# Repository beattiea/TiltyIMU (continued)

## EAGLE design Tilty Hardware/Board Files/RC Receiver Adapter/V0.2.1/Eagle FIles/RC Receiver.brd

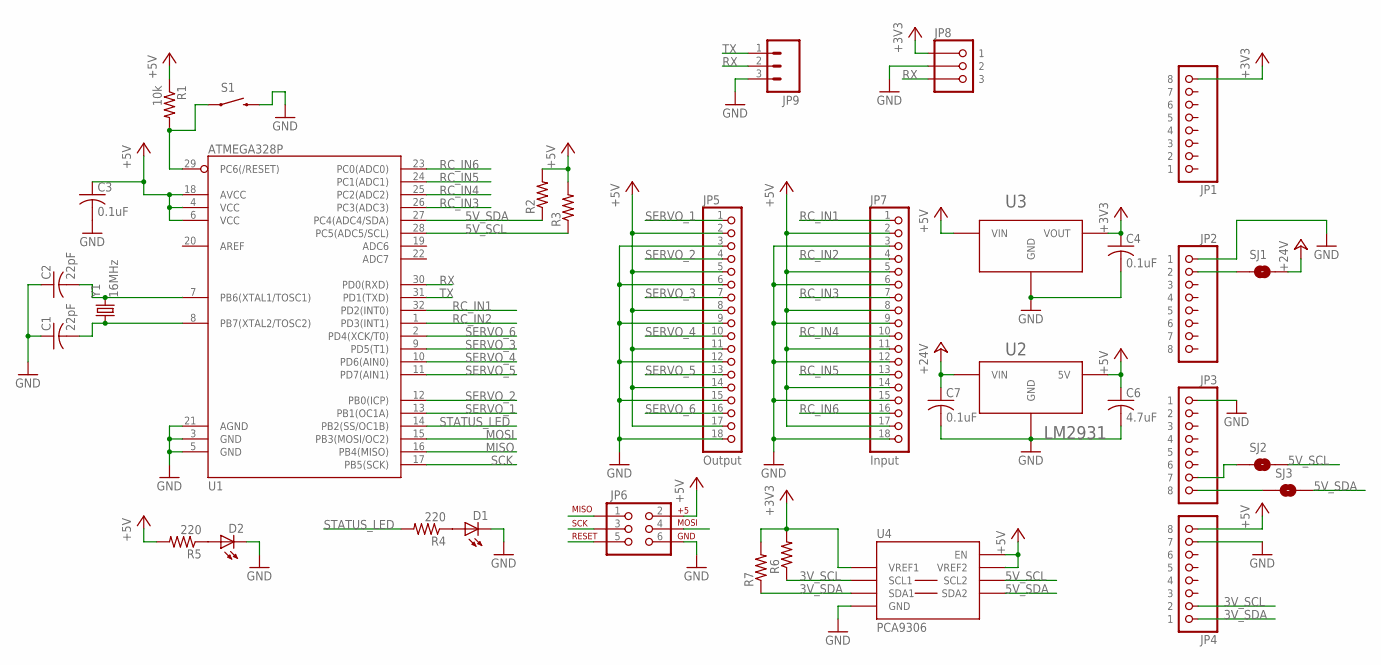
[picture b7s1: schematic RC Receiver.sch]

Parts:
C1, C2: 22pF; C0603
C3, C4, C7: 0.1uF; C0603
C6: 4.7uF; C0603
D1, D2: LED-GREENLED-0805_NO_SILK; LED-0805
JP1, JP2, JP3, JP4: 8-PIN_HEADER; 8-PIN_RECEPTACLE_LOCK_NO-SS
JP5: Output; 3X6_PTH_HEADER
JP6: AVR_SPI_PRG_62X3_LOCK; 2X3_LOCK
JP7: Input; 3X6_PTH_HEADER
JP8: 3-PIN_JST_ZH_PTH_CONNECTORRIGHT_ANGLE_PTH; 3-PIN_JST_ZH_CONNECTOR_TH; PART# 455-1670-ND
JP9: M03LOCK; 1X03_LOCK
R1: 10k; R0603
R2, R3, R6, R7: R-US_R0603; R0603
R4, R5: 220; R0603
S1: SWITCH-MOMENTARY-2SMD; TACTILE_SWITCH_SMD
SJ1: SOLDERJUMPERTRACE; SJ_2S-TRACE
SJ2, SJ3: SOLDERJUMPERNC2; SJ_2S-NOTRACE
U1: ATMEGA328P; TQFP32-08
U2: LM2931; TO263; PART# lm2931
U3: AP7313SOT23R; SOT23; PART# AP7313-33SRG-7
U4: PCA9306; SOIC-8
Y1: 16MHz; CRYSTAL-SMD-5X3; PART# 887-1104-1-ND

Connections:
3V_SCL: JP4.P$2 (2), R6.1, U4.P$3 (SCL1)
3V_SDA: JP4.P$1 (1), R7.1, U4.P$4 (SDA1)
5V_SCL: R3.1, SJ2.2, U1.28 (PC5(ADC5/SCL)), U4.P$6 (SCL2)
5V_SDA: R2.1, SJ3.2, U1.27 (PC4(ADC4/SDA)), U4.P$5 (SDA2)
+3V3: C4.1, JP1.P$8 (8), JP8.P$1 (1), R6.2, R7.2, U3.P$2 (VOUT), U4.P$2 (VREF1)
+5V: C3.1, C6.1, JP4.P$8 (8), JP5.2, JP5.5, JP5.8, JP5.11, JP5.14, JP5.17, JP6.2, JP7.2, JP7.5, JP7.8, JP7.11, JP7.14, JP7.17, R1.1, R2.2, R3.2, R5.2, U1.4 (VCC), U1.6 (VCC), U1.18 (AVCC), U2.P$3 (5V), U3.P$3 (VIN), U4.P$7 (VREF2), U4.P$8 (EN)
+24V: C7.1, SJ1.2, U2.P$2 (VIN)
GND: C1.1, C2.1, C3.2, C4.2, C6.2, C7.2, D1.2 (C), D2.2 (C), JP2.P$1 (1), JP3.P$1 (1), JP4.P$7 (7), JP5.3, JP5.6, JP5.9, JP5.12, JP5.15, JP5.18, JP6.6, JP7.3, JP7.6, JP7.9, JP7.12, JP7.15, JP7.18, JP8.P$2 (2), JP9.3, S1.3 (2), U1.3 (GND), U1.5 (GND), U1.21 (AGND), U2.P$1 (GND), U3.P$1 (GND), U4.P$1 (GND)
MISO: JP6.1, U1.16 (PB4(MISO))
MOSI: JP6.4, U1.15 (PB3(MOSI/OC2))
unnamed: C2.2, U1.7 (PB6(XTAL1/TOSC1)), Y1.3 (2)
unnamed: C1.2, U1.8 (PB7(XTAL2/TOSC2)), Y1.1
unnamed: D2.1 (A), R5.1
unnamed: JP2.P$2 (2), SJ1.1
unnamed: D1.1 (A), R4.1
unnamed: JP3.P$8 (8), SJ3.1
unnamed: JP3.P$7 (7), SJ2.1
RC_IN1: JP7.1, U1.32 (PD2(INT0))
RC_IN2: JP7.4, U1.1 (PD3(INT1))
RC_IN3: JP7.7, U1.26 (PC3(ADC3))
RC_IN4: JP7.10, U1.25 (PC2(ADC2))
RC_IN5: JP7.13, U1.24 (PC1(ADC1))
RC_IN6: JP7.16, U1.23 (PC0(ADC0))
RESET: JP6.5, R1.2, S1.1, U1.29 (PC6(/RESET))
RX: JP8.P$3 (3), JP9.2, U1.30 (PD0(RXD))
SCK: JP6.3, U1.17 (PB5(SCK))
SERVO_1: JP5.1, U1.13 (PB1(OC1A))
SERVO_2: JP5.4, U1.12 (PB0(ICP))
SERVO_3: JP5.7, U1.9 (PD5(T1))
SERVO_4: JP5.10, U1.10 (PD6(AIN0))
SERVO_5: JP5.13, U1.11 (PD7(AIN1))
SERVO_6: JP5.16, U1.2 (PD4(XCK/T0))
STATUS_LED: R4.2, U1.14 (PB2(SS/OC1B))
TX: JP9.1, U1.31 (PD1(TXD))

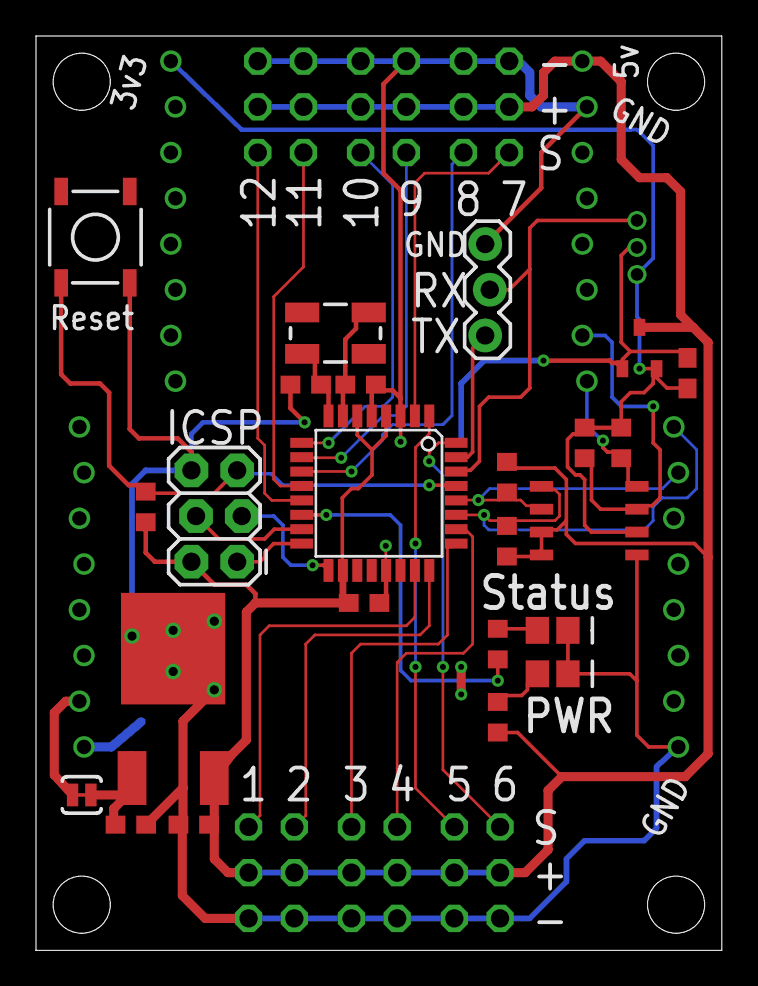
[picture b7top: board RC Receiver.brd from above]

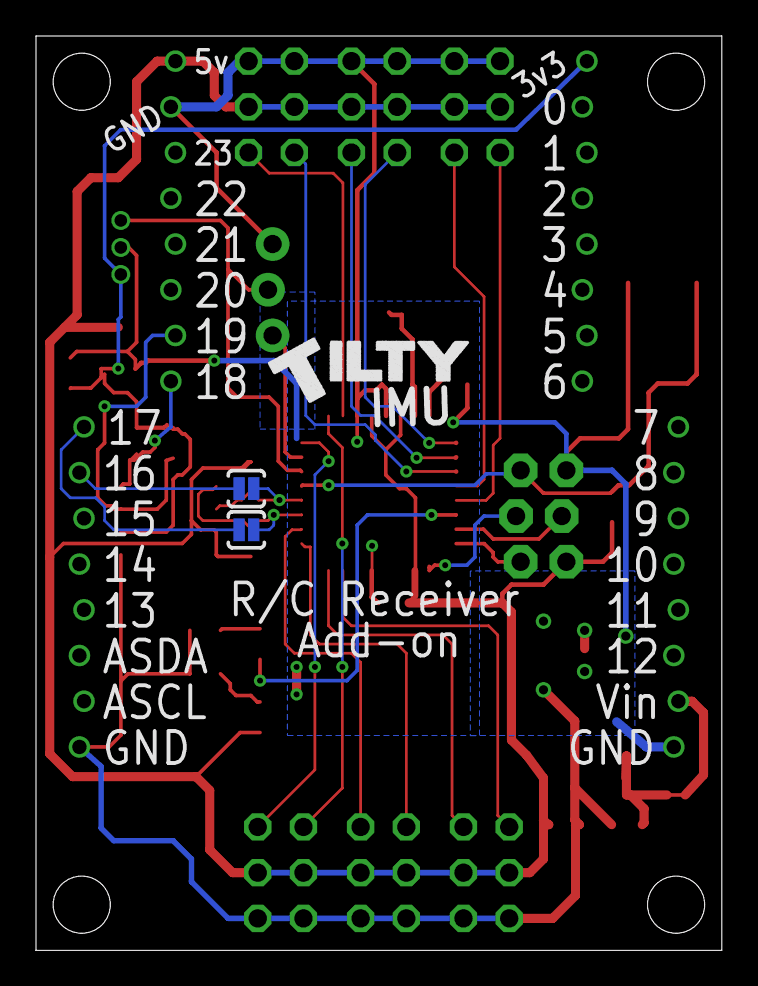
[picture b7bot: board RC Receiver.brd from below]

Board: 2 copper layers, 38.1 x 50.8 mm, 33 parts (2 on the bottom side), 34 nets.

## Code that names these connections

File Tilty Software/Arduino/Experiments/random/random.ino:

#include <SatelliteRX.h>
#include <RCadapter.h>

#include <Wire.h>
#include "EEPROM.h"

#include <Servo.h>
//#include <FastServo.h>

byte inputs[3] = {2, 3, 4};

RCadapter rx = RCadapter();

// Motor PWM pins
#define M1 6
#define M2 5
// Motor direction control pins
#define M1A 4
#define M1B 9
#define M2A 7
#define M2B 8

void setup() {
	/*	R/C adapter testing
	Serial.begin(115200);
	//delay(5000);
	Serial.println("Beginning...");
	rx.init();
	
	for (int i = 0; i < 3; i++) {
		Serial.print("input_pins: ");
		Serial.println(rx.input_pins[i]);
	}
	Serial.println();
	
	rx.initRCinputs(inputs, 3);
	
	for (int i = 0; i < 3; i++) {
		Serial.print("input_pins: ");
		Serial.println(rx.input_pins[i]);
	}
	Serial.println();
	*/
	TCCR0A = _BV(COM0A1) | _BV(COM0B1) | _BV(WGM01) | _BV(WGM00);// Setup pins 5 and 6 for fast PWM
	TCCR0B = _BV(CS00);// Set PWM frequency to 62.5kHz (fastest possible)
	
	pinMode(M1, OUTPUT);
	pinMode(M2, OUTPUT);
	
	pinMode(M1A, OUTPUT);
	pinMode(M1B, OUTPUT);
	pinMode(M2A, OUTPUT);
	pinMode(M2B, OUTPUT);
	
	digitalWrite(M1A, HIGH);
	digitalWrite(M1B, LOW);
	digitalWrite(M2A, LOW);
	digitalWrite(M2B, HIGH);
}

void loop() {
	/*	R/C adapter testing
	if (rx.readRCinputs()) {
		for (int i = 0; i < 3; i++) {
			Serial.print("Channel: ");
			Serial.println(rx.channel_values[i]);
		}
		Serial.println();
	}
	*/
	
	for (int i = 0; i < 256; i++) {
		analogWrite(M1, i);
		analogWrite(M2, i);
		delay(160);
	}
	
	for (int i = 255; i > -1; i--) {
		analogWrite(M1, i);
		analogWrite(M2, i);
		delay(160);
	}
	
	digitalWrite(M1A, !digitalRead(M1A));
	digitalWrite(M1B, !digitalRead(M1B));
	digitalWrite(M2A, !digitalRead(M2A));
	digitalWrite(M2B, !digitalRead(M2B));
	
}

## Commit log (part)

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2013-08-06 Create getRaw.ino
    An example for the HMC5883
2013-08-06 Added compass datasheet to library and updated to auto-adjust gain settings
2013-08-06 lalalala
2013-08-07 Updated compass library to be a bit more user-friendly and customizeable
2013-08-07 Deleted very bad initial 9DOF IMU fusion test code
2013-08-07 Fixed a bug in altimeter oversampling setting and updated sensor testing program to speed up readings
2013-08-07 Added beginnings of Plane testing. Updated MPU-6050 DMP to better handle data interrupt
2013-08-07 Updated compass cont calibration test program, added compass to plane test program
2013-08-07 Updated things.todo
2013-08-08 Continued GPS testing and added datasheet
2013-08-09 Changed folder name to not screw up repository
2013-08-09 Updated Things todo, added next revision of dual motor driver, started gps bee breakout
2013-08-10 Added flash memory testing code
2013-08-11 Added a functional (but not finished) flash memory library
2013-08-12 SpiFlash now stores all 32-bit values as floats, but can return floats or ints
2013-08-12 Fixed a problem where altimeter device address conflicted with a variable in the SpiFlash library
2013-08-12 Lots of little updates to software libraries. As well as updated plane testing code to include yaw
2013-08-13 Added altimeter sensor fusion
2013-08-13 I don't know what's going on!!!!!!
2013-08-13 Reverting back to working commit
2013-08-13 Sensor fusion with all sensors is functional!
2013-08-14 Aded beginning of compass calibration program, tweaked compass libraries
2013-08-14 Updated some sensor libraries to better handle initialization without the sensor attached
2013-08-15 Revert "F'ed up the IMU library trying to get it to work in the TiltyIMU functions"
    This reverts commit a638e84b166a2e9060302dd66009bc4444dee52a.
2013-08-15 Re-deleted some unnecessary programs
2013-08-17 Added all necessary libraries to TiltyIMU library folder to simplify includes
2013-08-18 Updated Plane self-level testing program
2013-08-19 Added functions to PID library to detect individual component limiting
2013-08-20 Added doxygen formatting to PID library for easy reference
2013-08-20 Quad testing code
2013-08-20 Changed quadcopter test file name
2013-08-21 Deleted unnecessary NMEA parser
2013-08-21 Updated PID values in Quadcopter testing program
2013-08-22 Added test program for Spektrum Satellite receiver
2013-08-25 Tweaked sensor fusion testing to get good data and added testing results
2013-08-26 Updated things.todo and RC Receiver add-on has been ordered
2013-08-27 Working on Altitude Limiting code
2013-08-29 Updated Tilty Duo/Quad PCB and TiltyIMU software library
    PCB: Added circuit protection
    Software: Fixed conflicts with duplicate file names
2013-09-01 Added lots of stuff!
    Added a completed Advanced IMU add-on prototype
    Added a Spektrum Satellite R/C receiver library
    Added Spektrum Satellite R/C receiver testing code
    Added a Tilty PCB template
    Fixed a bug in the PID library
2013-09-01 Took out some testing code in the PID library
2013-09-01 Ignore this!!!! Tinkering with a new code editor's GIT commands
2013-09-02 More work on the Tilty Omni
2013-09-02 Tilty PCB work
2013-09-03 Corrected a warning between the i2c_t3 and I2CDev libraries
2013-09-03 Updated bluetooth command jumper to a cuttable trace solder jumper
2013-09-10 Changed a filter cap value, Lots of bluetooth library work
2013-09-13 LOTS of work on the Tilty Omni
2013-09-13 Lots more Tilty Omni work!
2013-09-13 RC Receiver add-on tweaking, updating things.todo handling
2013-09-14 GPS breakout work, and minor Tilty Omni changes
2013-09-15 Still working on the Tilty Omni...
2013-09-19 Minor changes
    Added current limit resistor to zener shunt on Tilty Duo/Quad.
    Added power supply solder jumper to Advanced IMU altimeter.
2013-09-21 Finished preliminary Tilty Omni design!
    Still needs review before being ordered
2013-09-22 Added a non-blocking AVR I2C library for add-on boards
    I didn't write it, and it's untested so far
2013-09-22 Dual motor driver testing!
2013-09-25 Lots of little updates!
2013-09-26 Added USB Host add-on board
2013-09-26 Nearly finished USB Host
2013-09-27 GPS adapter work
2013-09-29 More RC adapter library work
    It's coming along. Now (sort of) allows servo control from a Tilty
    controller
2013-09-29 Updated USB Host add-on silkscreen for prototype ordering
2013-09-29 Dula motor driver revisions
2013-09-29 Ordered USB Host add-on prototype
    Added folder for next revision and updated Tilty Template to show
    reserved pins
2013-09-30 Updated Gerbers slightly
2013-10-01 Tweaked I2C call/response for motor driver testing
2013-10-01 Working Dual Motor Driver encoder reading over I2C
2013-10-01 Increased ground plane on Dual Motor Driver for heat dissipation
2013-10-01 Moved all multi-add-on test code to its own Experiments folder
2013-10-03 Removed unrelated code from RC adapter Teensy example/test program
2013-10-06 Added bottom paste layer to Duo/Quad gerbers
2013-10-06 Working R/C signal input test code, and added Atmega328 datasheet to R/C Adapter board files
2013-10-06 Updated R/C adapter silkscreen
2013-10-06 Updated RC adapter things.todo
2013-10-07 deleted most of the code in the random experiment program to test memory affects
2013-10-08 Added panelized solder paste gerber for stencil manufacture
    This is pretty useless to anyone but me, but it's good to have a cloud
    backup
2013-10-08 Began adding pwm RC input to R/C adapter library
2013-10-11 Removed some excess soldermask keepout on Dual Motor Driver, prototype review of Tilty Omni
2013-10-12 Modified random experiment program to test new motor driver
2013-10-12 Updated Tilty Omni things.todo post ordering prototypes
2013-10-12 Narrowed all I/O traces to be uniform width
2013-10-12 Fixed some silkscreen overlaps
2013-10-12 Added serial breakout to R/C adapter
2013-10-17 Updated Tilty Duo/Quad PCB files with production version
2013-10-17 Tweaked some silkscreen labeling
2013-10-18 Motor driver software work
    Implemented encoder reading/writing over I2C (only tested reading)
2013-10-18 Moved some outdated programs, fixed TiltyTest program to actually report correct results
2013-10-19 Began adding Teensy dual motor driver code
2013-10-20 Tiny I2C scanner update
2013-10-20 Deleted some unnecessary bluetooth documentation
2013-10-20 TiltyTest is ready for testing Tilty's post manufacture!
2013-10-21 Decreased memory test size
2013-10-21 Updated things.todo for motor driver board
2013-10-25 Deleted main things.todo, moving to individual lists on a per project/task basis
    Also the Tilty Omni and USB Host eagle files had some weird update,
    nothing actually changed
2013-10-26 Updated some things.todo on Tilty Duo/Quad solder paste layer
2013-10-27 Added voltage sense testing to TiltyTest program
2013-10-29 Shrunk IMU die pad solder paste layer on Duo/Quad
2013-10-29 Updated flash memory testing in TiltyTest program
2013-10-30 Updated TiltyTest program to output readable angles and optionally raw IMU data
2013-11-01 Lots of file rearranging and tweaks to be ready for official TiltyIMU launch!
2013-11-01 Updated RC Receiver Adapter datahseets
2013-11-02 Deleted a bunch of stuff from TiltyWay 2 to remove excess code
2013-11-07 Moved bluetooth pass-through program into completed programs as it works pretty well
2013-11-08 Created an experimental TiltyIMU_demo program for testing automatic code updating
2013-11-08 Added bluetooth command examples to compass network, deleted outdated bluetooth settings testing
2013-11-09 Updated bluetooth and compass datasheets
2013-11-11 Removed WProgram from the includes
2013-11-13 TiltyIMU_Demo now has beta version of firmware updating
2013-11-13 Revert "Added windows support for TiltyIMU Demo firmware updating"
    This reverts commit 0f1818baa688dd565cb7b1bb9a37b8f0be612a7b.
2013-11-13 Processing sketch updates
2013-11-14 Added a couple minor changes to Tilty Duo/Quad to do list
2013-11-15 Deleted redundant Tilty Omni backups
2013-11-15 Windows firmware update now works properly
2013-11-19 Extremely minor changes to initialization
2013-11-19 Deleted redundant Eagle backups
2013-11-21 Fixed compass tilt compensation
2013-11-21 Added option to set DMP sample rate with #define MPU6050_DMP_FIFO_RATE
    Uses values from 0x00 - 0x09.
    Sample frequency = 200 Hz / (1+rate)
2013-11-21 Fixed a tab error
2013-11-22 Working segway balance code, but not finished
2013-11-22 Changed from using bluetooth to USB
2013-12-06 LOTS of cleaning house....
2013-12-07 Updated Dual Motor Driver code to better handle I2C communicatioon
2013-12-08 Added beginnings of Segway Setup program
2013-12-12 Lots of tilt compensation testing
2013-12-12 tested setting up both sets of i2c pins at once
2013-12-12 I don't know why GIT thinks this changed...
2013-12-13 Added rudimentary speed control to Dual Motor Driver
    Uses encoder ticks between updates and linearly adds or subtracts power
    based on whether motor is faster or slower than it should be
2013-12-27 Increased register buffer size
2013-12-27 Random changes for testing
2013-12-30 Just moved the motor driver schematic around a bit for better printing
2013-12-30 Updated software license template
2014-01-02 Updated Dual Motor Driver to (hopefully) final revision
2014-01-12 Updated Part number for reverse voltage diode
2014-01-19 Added auto I2C pin switching for Teensy
2014-01-19 Tuned to work with the dual motor driver (again)
2014-02-01 More motor driver software work...
2014-02-04 Added updated TiltyWay parts
2014-02-05 Moved some TiltyWay CAD and added DXF files for laser cutting
2014-02-05 Revert 6684f17..5894c78
    This rolls back to commit 6684f172e68a292aebb5596f6bfc8c0aa55313ab.
2014-02-08 Accidental changes (cause Eagle loaded the wrong file) to a version that's out of date anyway, ignore this
2014-02-08 Changed new motor driver to v0.1.5
2014-02-10 Added a completely new and massively optimized re-write of the Dual Motor Driver Library
    Motor 1 turns!
2014-02-10 Surprisingly effective (though not really integrated PID rate control code in Dual Motor Driver Code
2014-02-11 Broke all the #ifdefs and watchdog timer, but PWM is back up to speed and timer setup is better handled now
2014-02-12 Committing all for revert
2014-02-12 Revert 5583401..6d4fa54
    This rolls back to commit 558340168ba1a6e0ab0dc843e2c30d81665b7222.
2014-02-12 Revert 1aaed61..b2f92b8
    This rolls back to commit 1aaed61ab26ce22b1d179dbf9beff1c45a8d03ae.
2014-02-12 Revert b2f92b8..0f160bf
    This rolls back to commit b2f92b840df9383560d34d76835bb85b17caf157.
2014-02-13 Began changing speed control settings to new version
    Enable and mode settings vs. old mode settings using two bits
2014-02-14 Most features are functional, this is a backup of a working copy before implementing the second motor to the degree of the motor1
2014-02-15 Fixed PID direction control
    Now it’s calculated power based, instead of speed and set direction
    based.
    Basically, the PID calculation handles direction control instead of
    checking the target direction.
2014-02-16 Working automatic loading at startup
2014-02-18 Added forced reset function/command to motor driver
2014-02-23 Added TiltyIMU version of Arduino ISP programmer sketch
2014-02-24 Changed names to remove code version number
2014-02-24 Added some new feature ideas and notes to fix some bugs
2014-02-26 Added Kinetis peripheral manual to Duo and Quad hardware folder
2014-03-02 Began implementing improved and custom I2C handling for motor driver
    Began implementing custom I2C (Wire) for motor driver as well s
    changing how motor control/status variables are handled to better allow
    them to be sent over I2C
2014-03-06 Changed motor driver to use custom Wire code to allow for a larger buffer and more optimized code
2014-03-09 Added beginnings of temporary basic full-size segwoid program
2014-03-09 Deleted a duplicate and unnecessary setSpeed function for the dual motor driver
2014-03-10 Fixed a miscalculation in reading Euler angles
2014-03-14 Working rideable code for temp_segwoid
2014-03-19 Minor tweaks to temporary segway code
2014-03-19 Added DMP to temporary segway code
    It’s not very effective…
2014-03-29 Slowed I2C rate in Tilty Testing program to a more reasonable 200kHz
2014-04-04 Deleted some unnecessary Tilty Duo/Quad files
2014-04-04 Added TiltyWay test plate .dxf files for laser cutting
2014-04-16 Slightly adjusted TiltyWay side panel
